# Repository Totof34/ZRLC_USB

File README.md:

ZRLC_USB
================

A small project to measure resistance, impedance, capacitance, inductance, input impedance of
amplifier, transformers, etc 

If you would have more information about this project please visit 
www.audiyofan.org

A link to the dedicated post 

http://www.audiyofan.org/forum/viewtopic.php?f=57&t=8121&start=30

It's just a box connected via USB , you don't need an external sound card to measure ZRLC,

You can use VisualAnalyser or an other program, A link to the dedicated to the software

http://www.sillanumsoft.org/ZRLC.htm

Under Linux no drivers is required
Under Windows you can find in the folder "Drivers_windows" all you need to run this box properly

PCB & schema are designed with Kicad

All comments are welcome

Totof

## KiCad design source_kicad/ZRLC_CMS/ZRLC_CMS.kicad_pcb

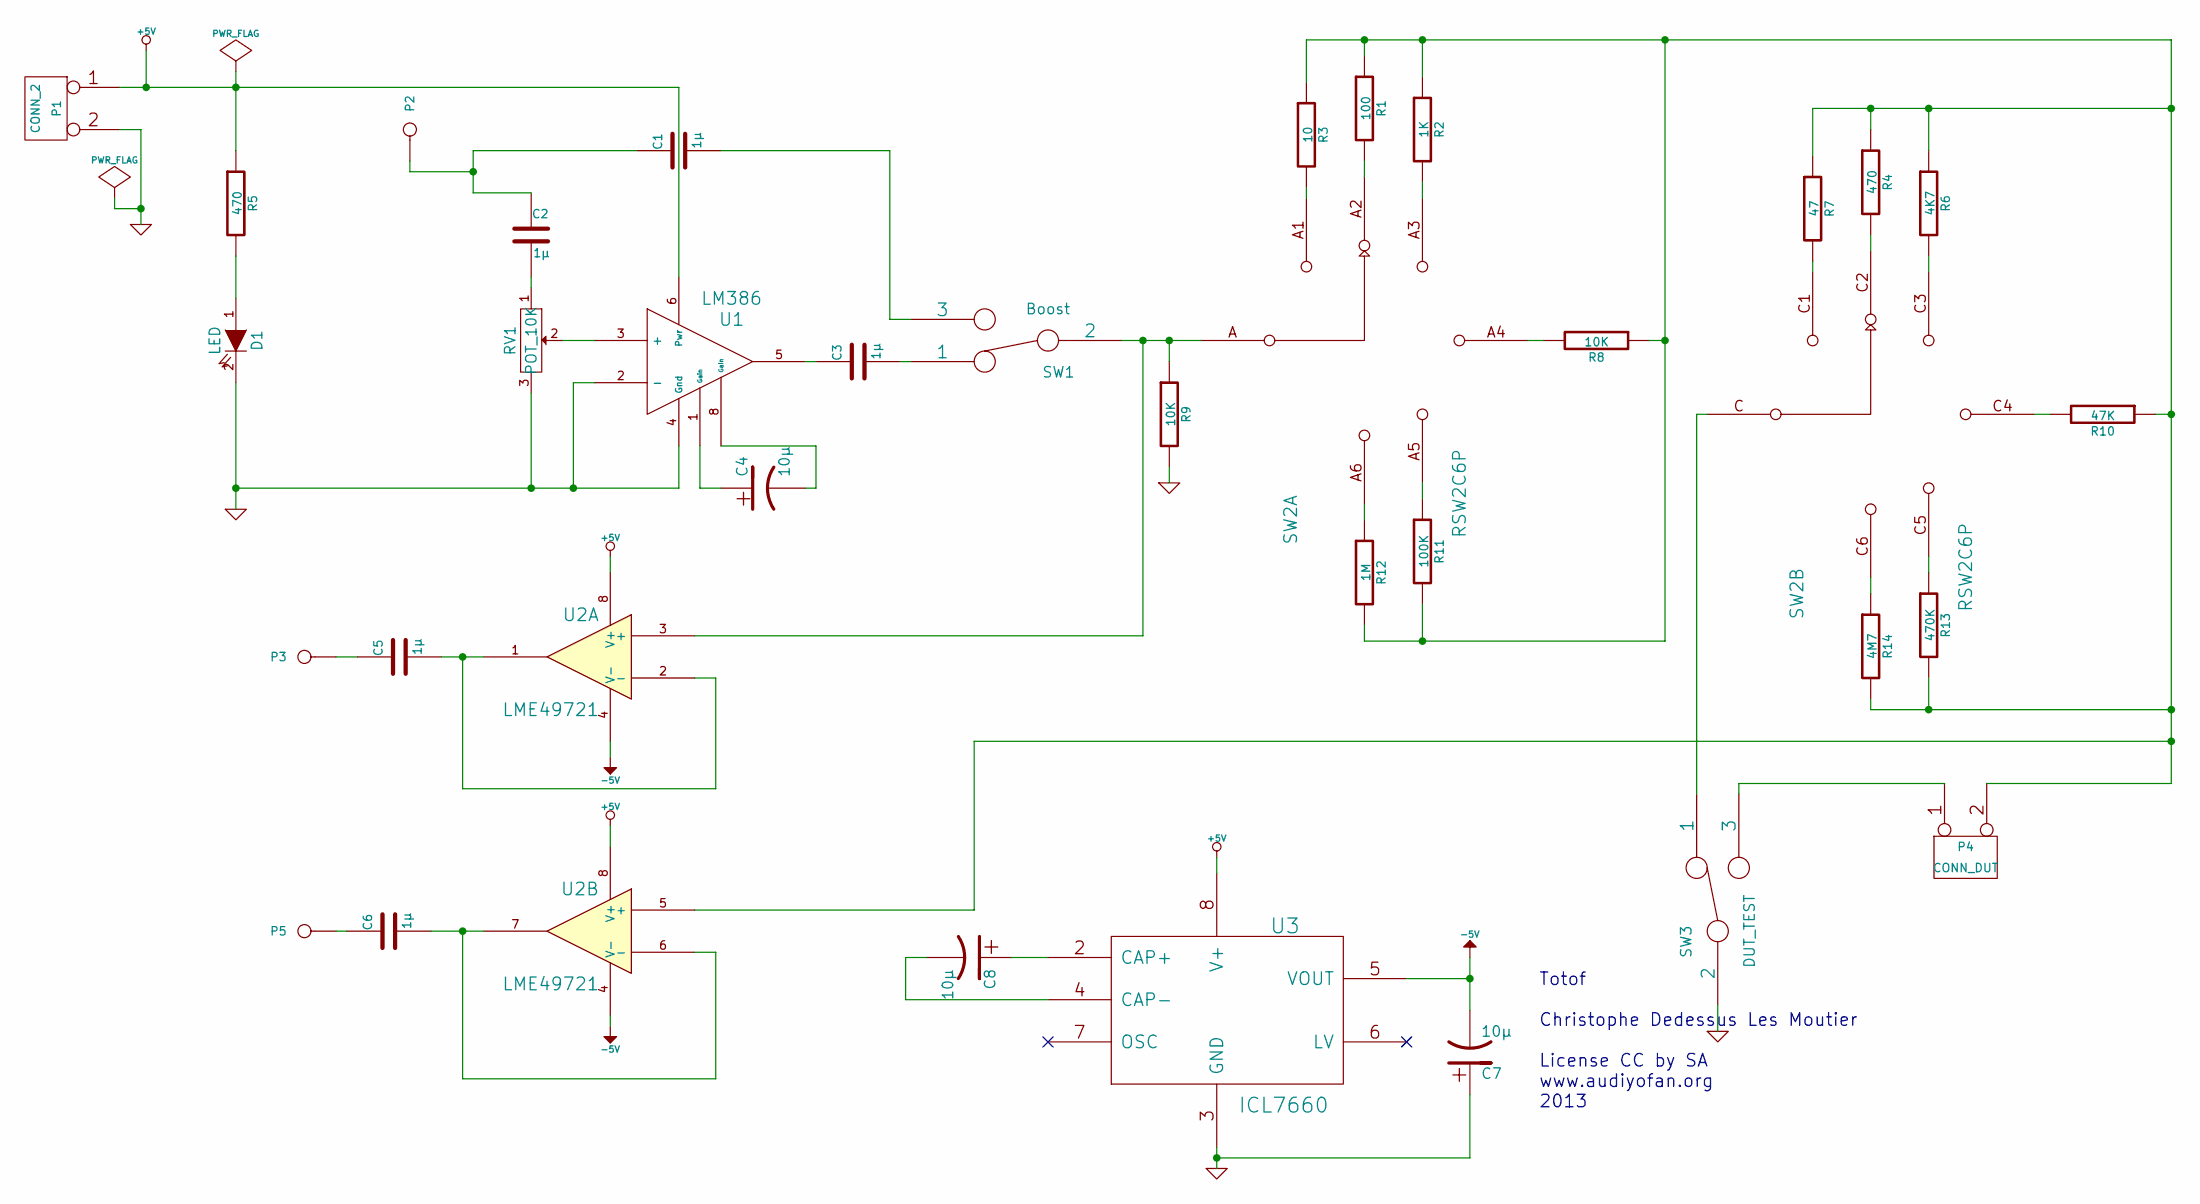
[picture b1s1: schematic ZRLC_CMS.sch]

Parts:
C1, C2, C3, C5, C6: 1µ
C4, C7, C8: 10µ
D1: LED
P1: CONN_2
P2: OUT_R
P3: IN_R
P4: CONN_DUT
P5: IN_L
R1: 100
R2: 1K
R3: 10
R4, R5: 470
R6: 4K7
R7: 47
R8, R9: 10K
R10: 47K
R11: 100K
R12: 1M
R13: 470K
R14: 4M7
RV1: POT_10K
SW1: Boost
SW2: RSW2C6P
SW3: DUT_TEST
U1: LM386
U2: LME49721
U3: ICL7660

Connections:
+5V: P1.1, R5.1, U1.6 (Pwr), U2.8 (V+), U3.8 (V+)
-5V: C7.2, U2.4 (V-), U3.5 (VOUT)
GND: C7.1, D1.2 (K), P1.2 (PM), R9.2, RV1.3, SW3.2, U1.2 (-), U1.4 (Gnd), U3.3 (GND)
unnamed: R10.2, SW2.C4
unnamed: R6.2, SW2.C3
unnamed: R4.2, SW2.C2
unnamed: R7.2, SW2.C1
unnamed: SW2.C, SW3.1
unnamed: P4.2 (PM), R1.1, R2.1, R3.1, R4.1, R6.1, R7.1, R8.1, R10.1, R11.2, R12.2, R13.2, R14.2, U2.5 (+)
unnamed: R12.1, SW2.A6
unnamed: R14.1, SW2.C6
unnamed: R13.1, SW2.C5
unnamed: R3.2, SW2.A1
unnamed: R1.2, SW2.A2
unnamed: R2.2, SW2.A3
unnamed: R8.2, SW2.A4
unnamed: R11.1, SW2.A5
unnamed: C8.1, U3.2 (CAP+)
unnamed: C8.2, U3.4 (CAP-)
unnamed: P4.1, SW3.3
unnamed: C6.1, P5.1
unnamed: D1.1 (A), R5.2
unnamed: C1.2, SW1.3
unnamed: C3.2, SW1.1
unnamed: RV1.2, U1.3 (+)
unnamed: C4.1, U1.1 (Gain)
unnamed: C3.1, U1.5
unnamed: C2.2, RV1.1
unnamed: C1.1, C2.1, P2.1
unnamed: C5.1, P3.1
unnamed: C4.2, U1.8 (Gain)
unnamed: R9.1, SW1.2, SW2.A, U2.3 (+)
unnamed: C5.2, U2.1, U2.2 (-)
unnamed: C6.2, U2.6 (-), U2.7

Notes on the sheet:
Totof Christophe Dedessus Les Moutier License CC by SA www.audiyofan.org 2013

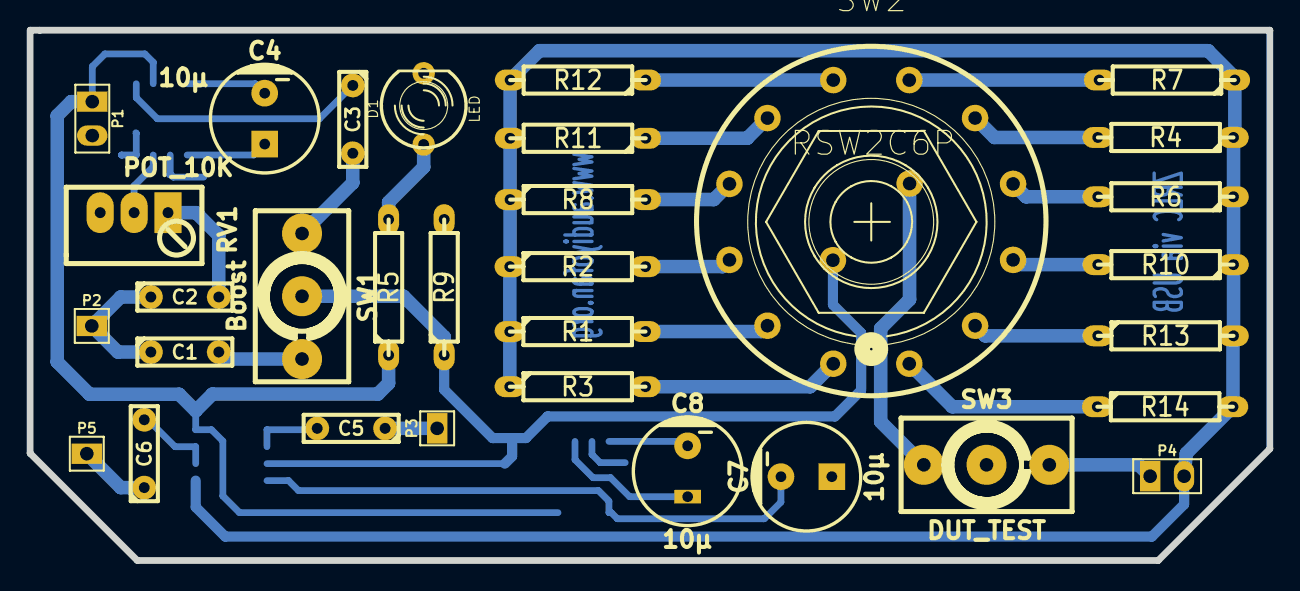
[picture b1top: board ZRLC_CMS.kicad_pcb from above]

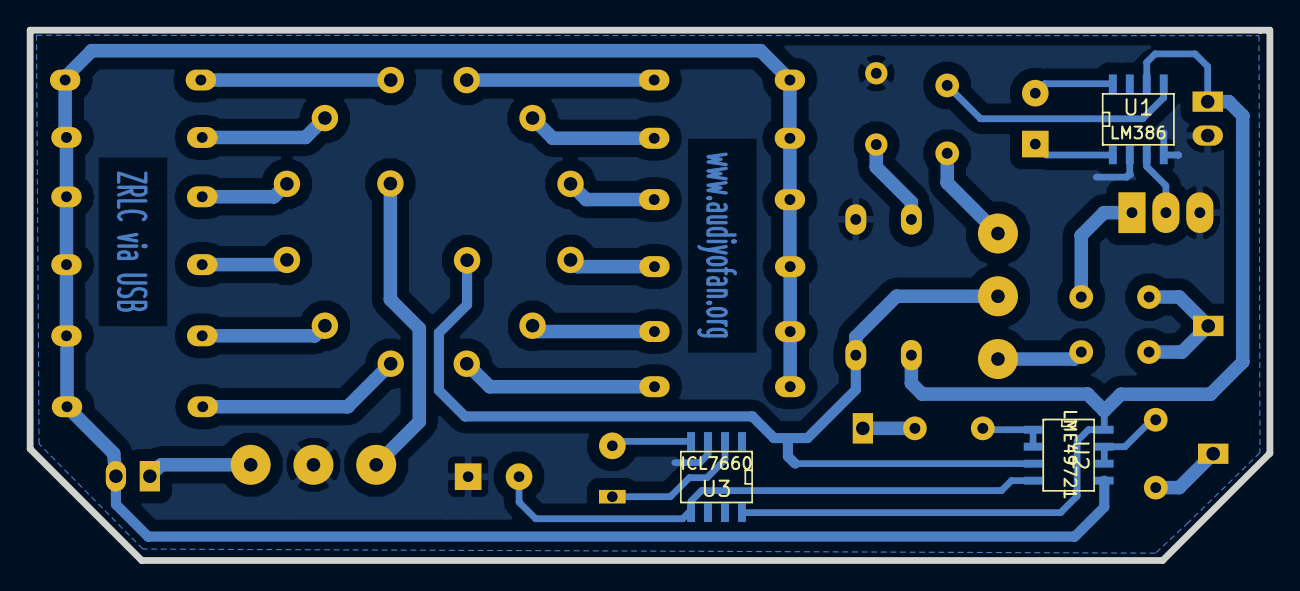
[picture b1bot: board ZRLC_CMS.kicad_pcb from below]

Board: 2 copper layers, 92.8 x 39.7 mm, 35 parts (3 on the bottom side), 34 nets.

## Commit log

2013-09-18 Init
2013-09-19 Add a link to VisualAnalyser
2013-12-21 Add new file and "build" folder
